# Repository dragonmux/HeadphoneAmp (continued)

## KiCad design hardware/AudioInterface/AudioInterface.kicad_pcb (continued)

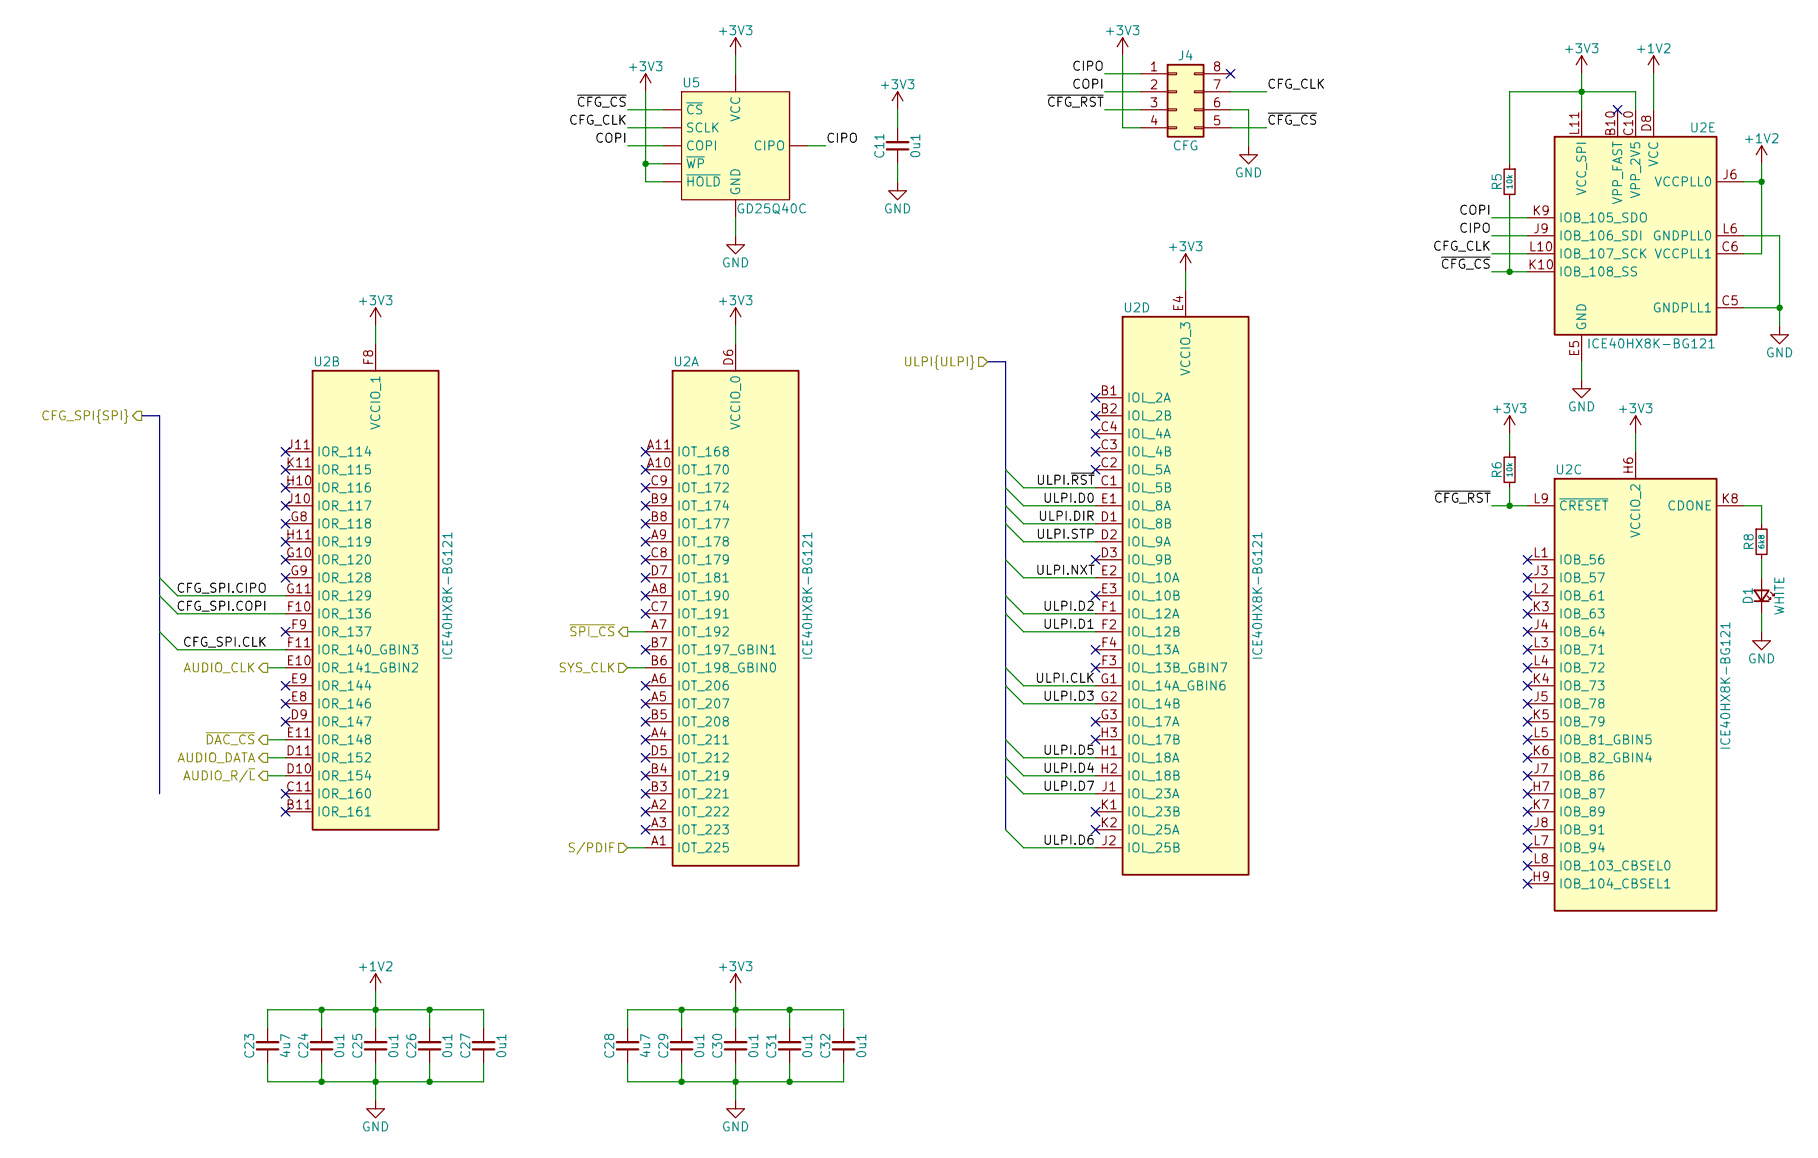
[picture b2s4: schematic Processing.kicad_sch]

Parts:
C11: 0u1; C0603; MPN CGA3E2X7R1E104K080AA
C23, C28: 4u7; C0603; MPN C1608X5R1C475K080AC
C24, C25, C26, C27, C29, C30, C31, C32: 0u1; C0402; MPN CC0402KRX7R7BB104
D1: WHITE; LED0603; MPN ORH-W46G
J4: CFG; PinHeader_2x04_P1.27mm_Vertical_SMD; MPN FTSH-104-01-L-DV
R5, R6: 10k; R0603; MPN CRCW060310K0FKEA
R8: 6k8; R0603; MPN CRCW06036K80FKEA
U2: ICE40HX8K-BG121; BGA-121_9.0x9.0mm_Layout11x11_P0.8mm_Ball0.4mm_Pad0.35mm_NS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; MPN ICE40HX8K-BG121
U5: GD25Q40C; UDFN-8-1EP_3x2mm_P0.5mm_EP1.4x1.4mm; MPN GD25Q40CEIGR

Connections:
+1V2: C23.2, C24.2, C25.2, C26.2, C27.2, U2.C6 (VCCPLL1), U2.D4 (VCC), U2.D8 (VCC), U2.H4 (VCC), U2.H8 (VCC), U2.J6 (VCCPLL0); also elsewhere on the board
+3V3: C11.2, C28.2, C29.2, C30.2, C31.2, C32.2, J4.4, R5.1, R6.1, U2.C10 (VPP_2V5), U2.D6 (VCCIO_0), U2.E4 (VCCIO_3), U2.F8 (VCCIO_1), U2.G4 (VCCIO_3), U2.H6 (VCCIO_2), U2.L11 (VCC_SPI), U5.3 (~WP), U5.7 (~HOLD), U5.8 (VCC); also elsewhere on the board
/ACLK: U2.E10 (IOR_141_GBIN2); also elsewhere on the board
/ADAT: U2.D11 (IOR_152); also elsewhere on the board
/AR/~L: U2.D10 (IOR_154); also elsewhere on the board
/Clock Generation/~SPI_CS: U2.A7 (IOT_192); also elsewhere on the board
/Processing/CFG_CLK: J4.7, U2.L10 (IOB_107_SCK), U5.6 (SCLK)
/Processing/CFG_SPI.CIPO: U2.G11 (IOR_129); also elsewhere on the board
/Processing/CFG_SPI.CLK: U2.F11 (IOR_140_GBIN3); also elsewhere on the board
/Processing/CFG_SPI.COPI: U2.F10 (IOR_136); also elsewhere on the board
/Processing/CIPO: J4.1, U2.J9 (IOB_106_SDI), U5.2 (CIPO)
/Processing/COPI: J4.2, U2.K9 (IOB_105_SDO), U5.5 (COPI)
/Processing/ULPI.CLK: U2.G1 (IOL_14A_GBIN6); also elsewhere on the board
/Processing/ULPI.D0: U2.E1 (IOL_8A); also elsewhere on the board
/Processing/ULPI.D1: U2.F2 (IOL_12B); also elsewhere on the board
/Processing/ULPI.D2: U2.F1 (IOL_12A); also elsewhere on the board
/Processing/ULPI.D3: U2.G2 (IOL_14B); also elsewhere on the board
/Processing/ULPI.D4: U2.H2 (IOL_18B); also elsewhere on the board
/Processing/ULPI.D5: U2.H1 (IOL_18A); also elsewhere on the board
/Processing/ULPI.D6: U2.J2 (IOL_25B); also elsewhere on the board
/Processing/ULPI.D7: U2.J1 (IOL_23A); also elsewhere on the board
/Processing/ULPI.DIR: U2.D1 (IOL_8B); also elsewhere on the board
/Processing/ULPI.NXT: U2.E2 (IOL_10A); also elsewhere on the board
/Processing/ULPI.STP: U2.D2 (IOL_9A); also elsewhere on the board
/Processing/ULPI.~RST: U2.C1 (IOL_5B); also elsewhere on the board
/Processing/~CFG_CS: J4.5, R5.2, U2.K10 (IOB_108_SS), U5.1 (~CS)
/Processing/~CFG_RST: J4.3, R6.2, U2.L9 (~CRESET)
/SYS_CLK: U2.B6 (IOT_198_GBIN0); also elsewhere on the board
/S/PDIF: U2.A1 (IOT_225); also elsewhere on the board
/~DAC_CS: U2.E11 (IOR_148); also elsewhere on the board
DGND: C11.1, C23.1, C24.1, C25.1, C26.1, C27.1, C28.1, C29.1, C30.1, C31.1, C32.1, D1.1 (K), J4.6, U2.C5 (GNDPLL1), U2.E5 (GND), U2.E6 (GND), U2.E7 (GND), U2.F5 (GND), U2.F6 (GND), U2.F7 (GND), U2.G5 (GND), U2.G6 (GND), U2.G7 (GND), U2.H5 (GND), U2.L6 (GNDPLL0), U5.4 (GND), U5.9 (GND); also elsewhere on the board
unnamed: D1.2 (A), R8.2
unnamed: R8.1, U2.K8 (CDONE)

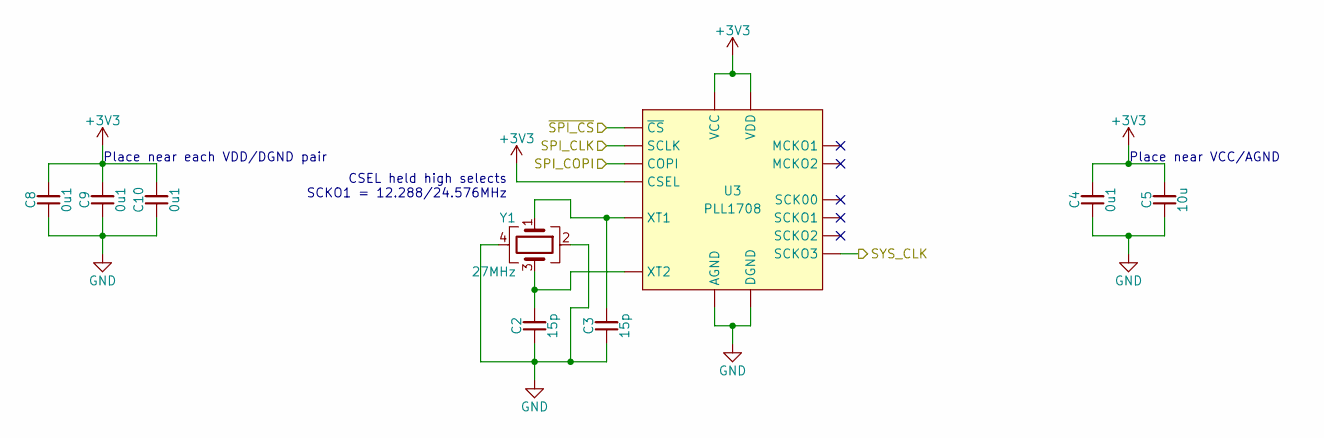
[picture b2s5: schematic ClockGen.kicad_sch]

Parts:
C2, C3: 15p; C0603; MPN 06035A150JAT4A
C4, C8, C9, C10: 0u1; C0603; MPN CGA3E2X7R1E104K080AA
C5: 10u; C0603; MPN GRM188R61E106KA73D
U3: PLL1708; SSOP-20_3.9x8.7mm_P0.635mm; MPN PLL1708DBQ
Y1: 27MHz; SMD3225; MPN 7V-27.000MDDQ-T

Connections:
+3V3: C4.2, C5.2, C8.2, C9.2, C10.2, U3.1 (VDD), U3.8 (VCC), U3.12 (CSEL), U3.13 (VDD), U3.20 (VDD); also elsewhere on the board
/Clock Generation/~SPI_CS: U3.7 (~CS); also elsewhere on the board
/Processing/CFG_SPI.CLK: U3.6 (SCLK); also elsewhere on the board
/Processing/CFG_SPI.COPI: U3.5 (COPI); also elsewhere on the board
/SYS_CLK: U3.3 (SCKO3); also elsewhere on the board
DGND: C2.1, C3.1, C4.1, C5.1, C8.1, C9.1, C10.1, U3.4 (DGND), U3.9 (AGND), U3.16 (DGND), U3.17 (DGND), Y1.2, Y1.4; also elsewhere on the board
unnamed: C2.2, U3.11 (XT2), Y1.3
unnamed: C3.2, U3.10 (XT1), Y1.1

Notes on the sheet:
CSEL held high selects SCKO1 = 12.288/24.576MHz
Place near VCC/AGND
Place near each VDD/DGND pair

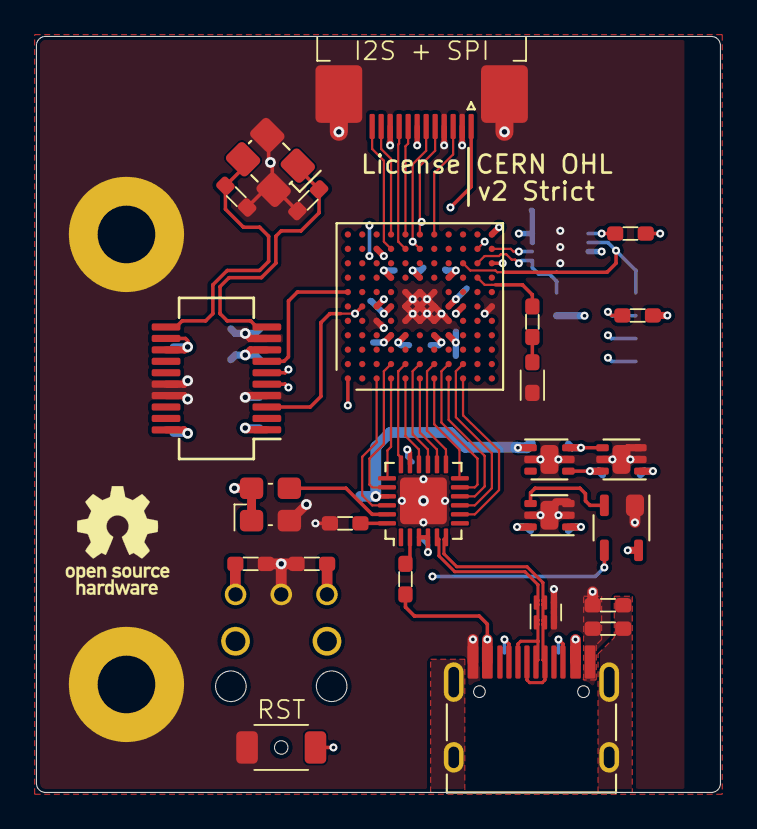
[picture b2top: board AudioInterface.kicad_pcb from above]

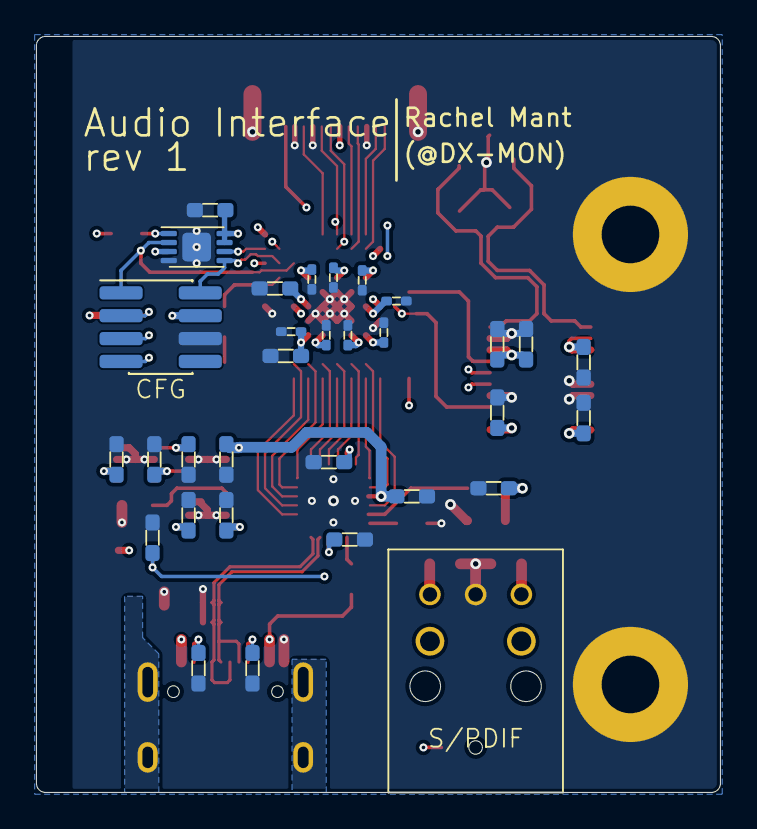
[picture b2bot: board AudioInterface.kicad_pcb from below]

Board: 4 copper layers, 38.0 x 42.0 mm, 60 parts (32 on the bottom side), 47 nets.

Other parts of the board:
G1: OSHW-Logo_5.7x6mm_SilkScreen

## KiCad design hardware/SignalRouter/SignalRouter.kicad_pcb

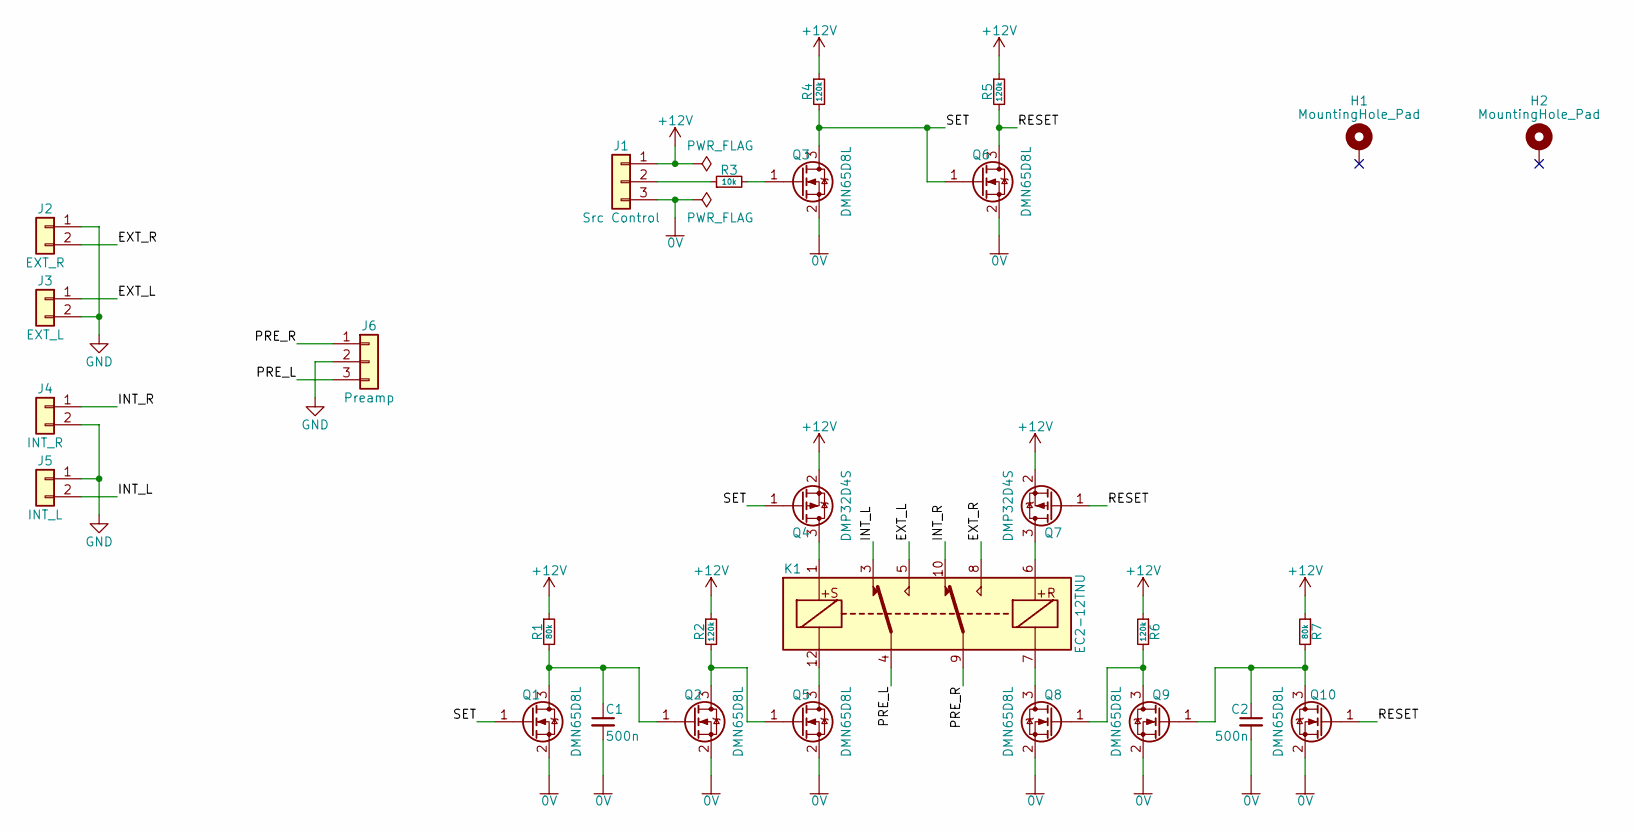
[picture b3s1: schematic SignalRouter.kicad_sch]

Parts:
C1, C2: 500n; C0603; MPN 0603B474K250CT
H1, H2: MountingHole_Pad; MountingHole_3.2mm_M3_Pad
J1: Src Control; PinHeader_1x03_P2.54mm_Vertical
J2: EXT_R; PinHeader_1x02_P2.54mm_Vertical
J3: EXT_L; PinHeader_1x02_P2.54mm_Vertical
J4: INT_R; PinHeader_1x02_P2.54mm_Vertical
J5: INT_L; PinHeader_1x02_P2.54mm_Vertical
J6: Preamp; PinHeader_1x03_P2.54mm_Vertical
K1: EC2-12TNU; Relay_DPDT_Kemet_EC2_DoubleCoil; MPN EC2-12TNU
Q1, Q2, Q3, Q5, Q6, Q8, Q9, Q10: DMN65D8L; SOT-23; MPN DMN65D8L-7
Q4, Q7: DMP32D4S; SOT-23; MPN DMP32D4S-7
R1, R7: 80k; R0603; MPN CRCW060380K6FKEA
R2, R4, R5, R6: 120k; R0603; MPN CRCW0603120KFKEA
R3: 10k; R0603; MPN CRCW060310K0FKEA

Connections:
0V: C1.2, C2.2, J1.3, Q1.2 (S), Q2.2 (S), Q3.2 (S), Q5.2 (S), Q6.2 (S), Q8.2 (S), Q9.2 (S), Q10.2 (S)
+12V: J1.1, Q4.2 (S), Q7.2 (S), R1.1, R2.1, R4.1, R5.1, R6.1, R7.1
/EXT_L: J3.1, K1.5
/EXT_R: J2.2, K1.8
/INT_L: J5.2, K1.3
/INT_R: J4.1, K1.10
/PRE_L: J6.3, K1.4
/PRE_R: J6.1, K1.9
/RESET: Q6.3 (D), Q7.1 (G), Q10.1 (G), R5.2
/SET: Q1.1 (G), Q3.3 (D), Q4.1 (G), Q6.1 (G), R4.2
GND: J2.1, J3.2, J4.2, J5.1, J6.2
unnamed: C1.1, Q1.3 (D), Q2.1 (G), R1.2
unnamed: C2.1, Q9.1 (G), Q10.3 (D), R7.2
unnamed: J1.2, R3.1
unnamed: K1.1, Q4.3 (D)
unnamed: K1.6, Q7.3 (D)
unnamed: K1.7, Q8.3 (D)
unnamed: K1.12, Q5.3 (D)
unnamed: Q2.3 (D), Q5.1 (G), R2.2
unnamed: Q3.1 (G), R3.2
unnamed: Q8.1 (G), Q9.3 (D), R6.2

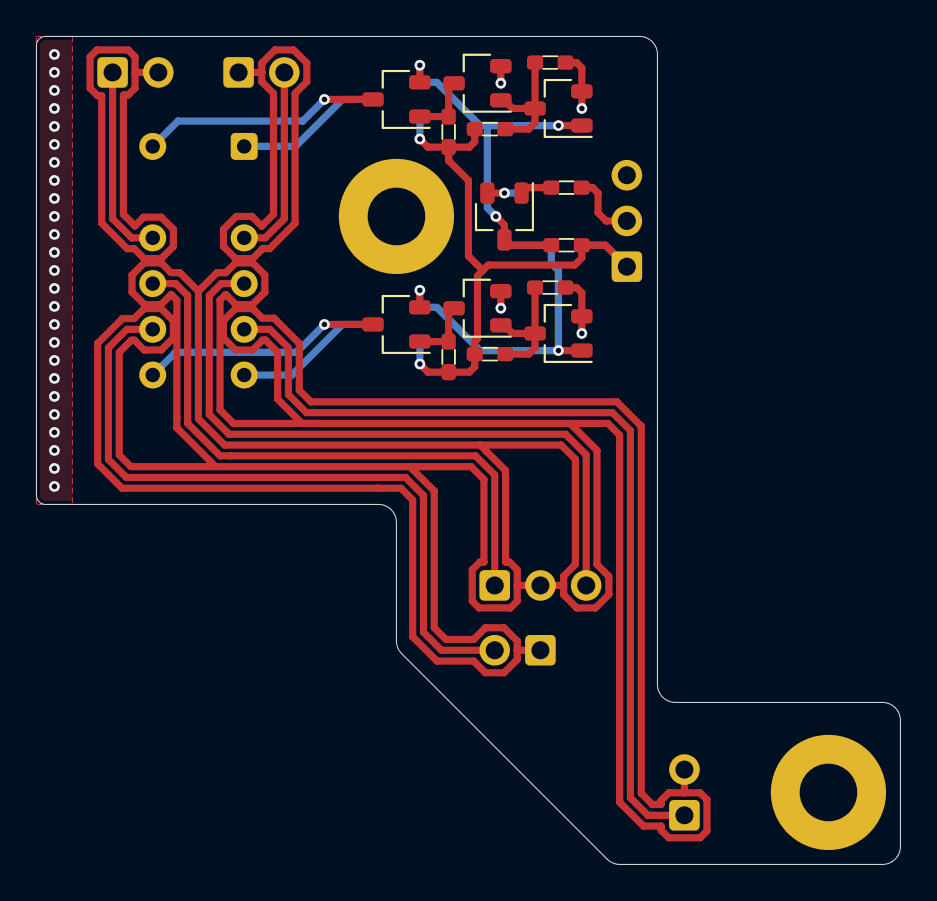
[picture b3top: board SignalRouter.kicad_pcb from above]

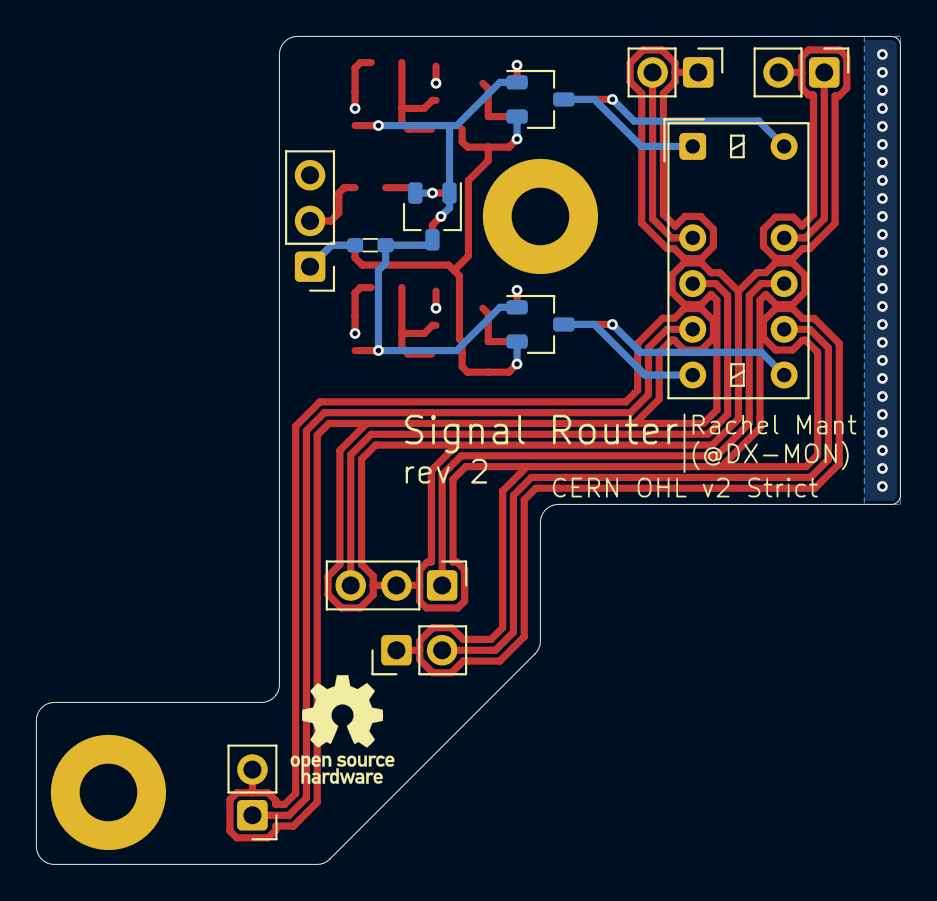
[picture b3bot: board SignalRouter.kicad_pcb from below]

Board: 4 copper layers, 48.0 x 46.0 mm, 28 parts (11 on the bottom side), 21 nets.

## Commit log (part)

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2022-01-12 Created the schematics for the amplifier + DAC
2022-01-12 Added the KiCad project file for the headphone amp + DAC board
2022-01-12 Added some sanity ignores for the hardware
2022-01-12 Added the signal routing daughter board for the headphone amp
2022-01-12 Added suitable licencing for the project
2022-01-12 Made the headphone amp + DAC board's refdes fabulous
2022-01-12 Added ignores for the gerber outputs
2022-01-12 Switched a pile of footprints over to our own versions
2022-01-15 Cleanup in the base board
2022-01-15 Created schematics for an audio interface board for the DAC part of the project
2022-01-15 Created the PCB layout for the audio interface board
2022-01-15 Improved the PSU enable/reset handling on the audio interface board
2022-03-04 Added the bare bones of the Amaranth based gateware for the project
2022-03-04 Added all the resources connected to the FPGA - in one format or another
2022-03-05 Begun building out the USB gateware to get this talking USB Audio v3.0
2022-03-05 gateware: platform: Fixed the ULPI resource not outputting a ~rst signal instead of a rst signal
2022-03-05 gateware: Added the logic required to make sure USB actually comes up
2022-03-05 gateware: usb.descriptors: Buillt several descriptors and helper types that were missing in the UAC3 logic in python-usb-protocol
2022-03-05 gateware: usb: Added more of the descriptors required to configure the USB audio device
2022-03-05 gateware: interface: Fixed a missing Amaranth import
2022-03-05 gateware: usb: Fixed some errors with the descriptor definitons
2022-03-05 Fixed the header descriptor 'forgetting' the subordinate ones
2022-03-05 gateware: usb: Added the proper alt-mode descriptors and audio streaming descriptor so we show up as a proper audio device
2022-03-05 gateware: Fixed the ULPI timings by making the clock a proper global clock
2022-03-06 gateware: usb: Implemented the power domain descriptor
2022-03-06 Implemented a stream deserializer for control request handling with trailing data
2022-03-06 gateware: sim: Added a sim for usb.control.request.AudioRequestHandler
2022-03-06 gateware: usb.control: Fixed a couple of mistakes in the AudioInterfaceHandler and StreamDeserializer
2022-03-07 gateware: usb.control.request: Fixed some mistakes with the indexing we do
2022-03-07 gateware: usb.control.request: Stubbed in support for switching alt-modes in AudioRequestHandler
2022-03-07 gateware: usb.control.request: Enabled the new alt-modes support
2022-03-07 gateware: sim.usb.control.request: Improvements to the AudioRequestHandler sim
2022-03-07 gateware: usb.control.request: Implemented handling for the feature unit's mute and volume controls
2022-03-07 gateware: sim.usb.protocol.request: Implemented testing for the new functionality
2022-03-07 gateware: sim.usb.control.request: Further refactoring of the sim
2022-03-07 gateware: sim.usb.control.request: More testing that the class-specific requests work properly
2022-03-07 gateware: sim.usb.control.request: Added sim for the volume range data retreival
2022-03-07 gateware: Found a new seed that builds with
2022-03-11 gateware: audio.i2s: Implemented a signal to request the next sample pair
2022-03-11 gateware: audio: begun implementing the audio domain logic
2022-03-11 gateware: usb: Exposed the AudioRequestHandler from the USB interface module
2022-03-11 gateware: usb: Added support for adding extra endpoints to the USBInterface module
2022-03-11 gateware: platform: Added a definition for the default clock and fixed some build options to help with timings
2022-03-11 gateware: interface: Added use of the audio module
2022-03-11 gateware: audio.endpoint: Implemented the state machine required to rescue data from the audio endpoint
2022-03-11 gateware: audio: Implemented the logic needed to get data from the USB endpoint to the sample FIFO
2022-03-12 gateware: audio: Fixed several bugs in the AudioStream module that caused the sample data to get corrupted on the way in
2022-03-12 gateware: audio.is2: Fixed the ordering of the channels going in to the initiator
2022-03-12 gateware: audio.i2s: Fixes to the I2S bus driver/initiator so it works correctly when driven with data from USB
2022-03-12 gateware: audio: Fixes to how the I2S bus driver is configured and driven by AudioStream
2022-03-21 gateware: audio: Fixed the timing generation for the audio bit clock so it now outputs the right frequency for a given system clock
2022-04-02 gateware: Cleaned up the descriptor and EP0 request/response handling having moved the definitions into python-usb-protocol
2022-04-02 gateware: audioInterface.usb: StreamDeserializer is now part of LUNA, so remove it from local
2022-04-12 gateware: sim.usb.control.request: Refactored out the ZLP reception logic into a proper function
2022-04-18 gateware: usb: Implemented DFU support to allow getting into the bootloader to upgrade the gateware
2022-04-18 general: added a sanity ignore for our VSCode dir
2022-05-31 gateware: platform: Switched from passing lists of opts to Platform.build() to passing strings as the API changed
2022-07-05 Implemented windows platform-specific descriptors for binding the DFU interface automatically
2022-09-25 gateware: sim.audio.i2s: Updated the sim to reflect how the clock divider now works
2022-09-25 gateware: usb.control.dfu: Corrected the behaving of DFU_DETACH as it was incorrectly implemented
2022-09-25 gateware: sim.usb.control.dfu: Begun implementing a sim for the DFU stub
2022-09-25 gateware: sim: Fixed a small niggle and an Amaranth warning
2022-09-25 gateware: Fixed our lack of support for the USB configurations system
2022-10-01 gateware: audio.i2s: Corrected the timings for the generation of the I²S rnl signal and re-timed the things that hang off it
2022-10-01 gateware: audio.i2s: Added some type annotations and fixed an unused variable warning
2022-10-01 gateware: audio.i2s: Begun documenting the state machine logic
2022-10-01 gateware: audio.i2s: Added a transition from run back to idle when the number of sample bits is reset to 0 or the clock divider reset to 0
2022-10-01 gateware: sim.audio.stream: Added the extra audio clock cycle timing to the sim to handle the addition of the setup state
2022-10-01 gateware: sim.audio.i2s: Cleaned up the gateware to run through the sample bits in reverse order directly, simplifying the cases for the last two bits
2022-10-01 gateware: sim.audio: Fixed the audio gateware sims so they can handle the I²S bus being requested with xdr = 1
2023-03-19 gateware: Switched the gateware over to Torii HDL + Sol USB + usb-construct
2023-03-19 gateware: audio.i2s: Correct for a CDC vs state machine timing issue that results in a output glitch
2023-03-19 gateware: audio: Improvements for timing
2023-10-16 gateware: Fixed a variable naming mistake in the entry script for the gateware
2023-10-16 gateware: cli: Refreshed the CLI to drop the dependency on Arachne and start moving to ToriiTestCase
2023-10-16 gateware: sim.audio.i2s: Reworked the simulation using ToriiTestCase
2023-10-16 gateware: cli: Switched from the old Arachne-based simulation framework to using unittest
2023-10-16 requirements: Updated the project requirements file
2023-10-16 gateware: sim.audio.stream: Removed an unused import
2023-10-16 gateware: sim.audio: Fixed up some type annotations for intelisense
2023-10-16 gateware: sim.usb.control.request: Reworked the simulation using ToriiTestCase
2023-10-19 gateware: platform: Updated the platform for Torii 0.5.0 and implemented a nextpnr seed option in the gateware CLI
2023-10-19 gateware: usb.control.windows.descriptorSet: Fixed a signed-unsigned conversion issue
2023-10-23 gateware: audio.spdif: Implemented the first part of 'Z' sync sequence handling
2023-10-23 gateware: sim.audio.spdif: Begun building a simulation for testing 'Z' sync sequence lockon
2023-10-23 gateware: sim.audio.spdif: Updated the tests, and expanded the simulation out further
2023-10-23 gateware: sim.audio.spdif: Refactored the sync sequence generators into their own functions
2023-10-23 gateware: audio.spdif: Implemented the logic to generate the sync and begin signals
2023-10-23 gateware: audio.spdif: Implemented the logic to handle subframe bit timing and bit timeout
2023-10-24 gateware: audio.spdif: Fixed a timing problem on the longTime signal and simplemented bit clock generation
2023-10-24 gateware: sim.audio.spdif: Implemented an 'X' sync sequence generator for the sim
2023-10-24 gateware: sim.audio.spdif: Fixed a small naming mistake in testSyncZ
2023-10-24 gateware: sim.audio.spdif: Began building out a simulation of getting a S/PDIF block
2023-10-24 gateware: audio.spdif: Added some comments that were missing for what states do in the timing FSM
2023-10-24 gateware: audio.spdif: Implemented dispatch for the start-of-subframe sync sequences at the end of a subframe
2023-10-24 gateware: audio.spdif: Fixed an issue with how channel gets reset to 0
2023-10-24 gateware: audio: Instantiated the SPDIF gateware into the design
2023-10-24 gateware: audio.spdif: Began implementing 'X' sync
    This implementation works but still needs bit timing validation done as it only detects when the timer would be exceeded, not if the transition happened too soon
2023-10-25 gateware: audio.spdif: Implemented a signal for determining if the end of a sync is a block start, and fixed the frame begin signal
2023-10-25 gateware: audio.spdif: Finished implementing 'X' sync with proper timing checks on the individual bits in the sequence
2023-10-25 gateware: audio.spdif: Fixed the subframe timing handler not incrementing the frame count at the end of each frame
2023-10-25 gateware: sim.audio.spdif: Added timeouts to the wait_until_* calls
2023-10-25 gateware: audio.spdif: Implemented a Biphase Mark Code decoder
2023-10-25 gateware: audio.spdif: Fixed a small nomenclature problem in the BMC decoder
2023-10-25 gateware: sim.audio.spdif: Cleaned up some unused imports in the timing sim
2023-10-26 gateware: audio.spdif: Added a resynchronised data output from the timing block for the incomming S/PDIF stream
2023-10-27 gateware: audio.spdif: Begun building a buffering audio block handler for the decoded data
2023-10-27 gateware: audio.spdif: Fixed a missing new line between the class description and `__init__` of BMCDecoder
2023-10-27 gateware: sim.audio.spdif: Began building a simulation for the audio block handler
2023-10-27 gateware: audio.spdif: Added a timing signal for when a S/PDIF block ends
2023-10-27 gateware: audio.spdif: Added a state and signals for initiating transfer from the block handler FIFOs to the I²S sample FIFO
2023-10-27 gateware: audio.spdif: Instantiated the new block handler and plumbed it in
2023-10-27 gateware: audio.spdif: Removed the unused frameBegin signal and updated the simulation to instead check blockEnd behaves properly
2023-10-27 gateware: audio.spdif: Corrected the sample validity check and control bits indexing
2023-10-27 gateware: audio.spdif: Fixed some signal nomenclature problems
2023-10-27 gateware: audio.spdif: Implemented decoding of the channel A type (left/right sample data)
2023-10-27 gateware: audio.spdif: Completed implementing getting data back out the channel FIFOs for consumption by the audio stream block
2023-10-27 gateware: audio.spdif: Implemented the top-level sample output interface
2023-10-27 gateware: audio.spdif: Fixed the data alignment problem in BlockHandler's output
2023-10-27 gateware: sim.audio.spdif: Added channel status bits into the data fed into the S/PDIF block handler
2023-10-27 gateware: audio.spdif: Fixed a couple of mistakes that had the data transfer logic broken
2023-10-27 gateware: audio.spdif: Switched the BlockHandler FIFOs over to SyncFIFOBuffered so they output data in the correct cycle
2023-10-28 gateware: audio: Completed a simple hook-up of the S/PDIF core to the I²S ouput FIFO
2023-10-28 gateware: platform: Ask nextpnr to write the placed and routed design to a .json file in the build directory
